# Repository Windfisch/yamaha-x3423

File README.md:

Faderboard Controller for a Yamaha X3423
========================================

This project takes out the X3423 motorized faderboard from a Yamaha 01v96 mixer and lets you wire it
up via USB. Additionally, it will have a display for each two faders that can display information
such as the assigned control.

Features right now:
	- Fader values are sent and received via MIDI CCs 1-17; sending a CC via MIDI will move the
	  fader to the respective position.
	- Integrating position regulator allows precise movement of the faders (which would otherwise
	  stop a bit before the actual target position due to friction).
	- Faders can work continously or in discrete steps; CCs 71-87 control the number of steps (where
	  0 means "continuous").
	- Calibration data is stored to flash. Perform a calibration by sending CC 100.

Hardware setup
--------------

Use a 1.25 pitch FFC A ribbon cable with 34 pins (*Note: these are quite difficult to get, I bought
a 40-lane-cable and cut it down.*) to connect the PCB with the faderboard on CN001; either use the
proper connector (*not JST*) to connect J12 with CN002, or solder an appropriate connector/cables to
CN002. Connect J16 and J17 to a buck/boost converter accepting 16V and outputting +15V/-15V, e.g.
DD39AJPA (DD1912PA should work too) from your favourite chinese marketplace.

Be sure to simultaneously power up both the main PSU and the USB board for now.

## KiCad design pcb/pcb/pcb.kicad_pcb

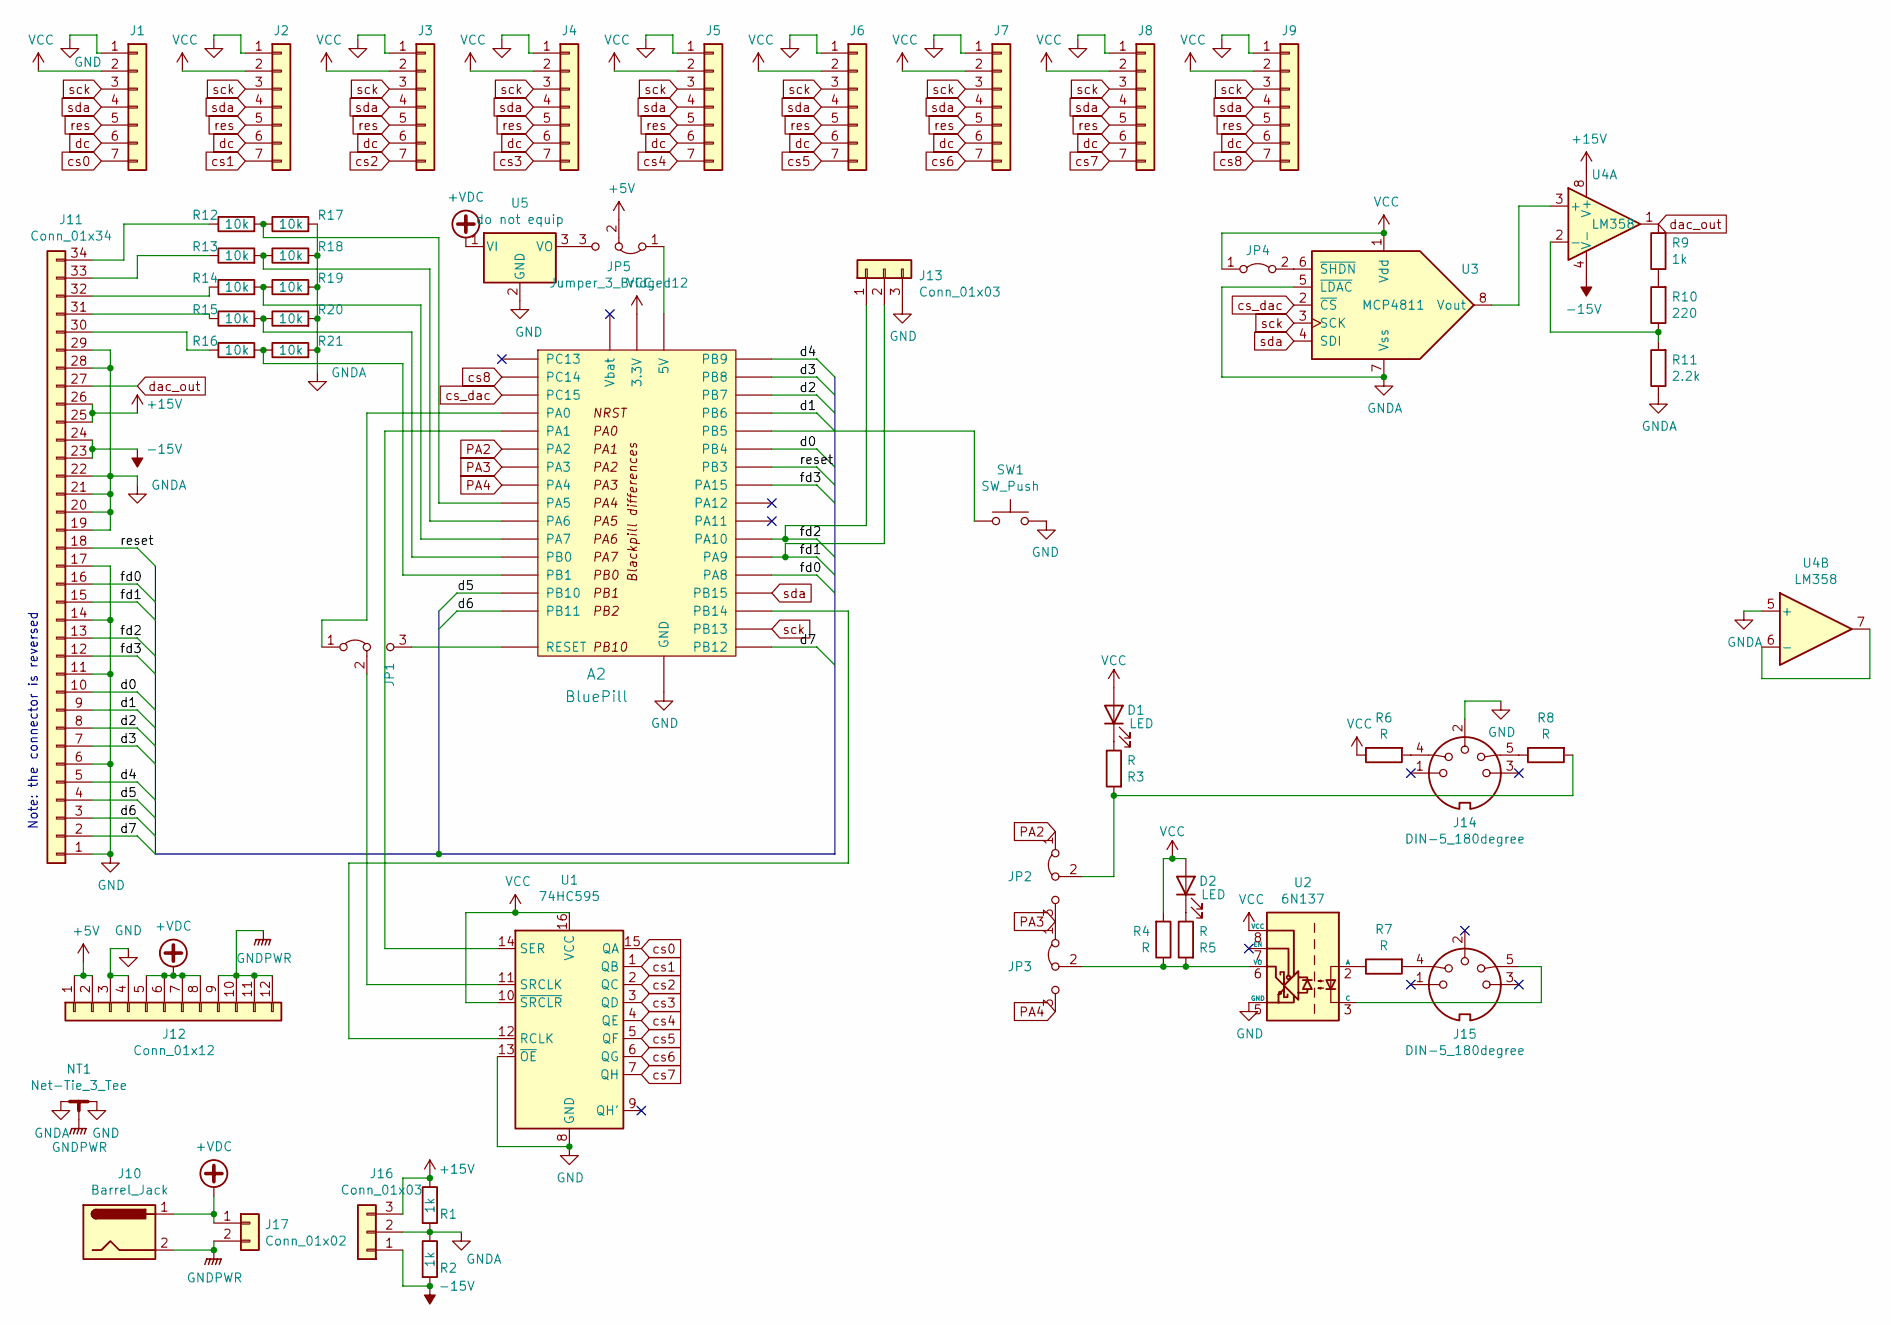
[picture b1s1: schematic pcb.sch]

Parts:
A2: BluePill; BLUEPILL-blackpill
D1, D2: LED; LED_D3.0mm_Horizontal_O1.27mm_Z2.0mm_IRBlack
J1, J2, J3, J4, J5, J6, J7, J8, J9: Conn_01x07; JST_XH_B7B-XH-A_1x07_P2.50mm_Vertical
J10: Barrel_Jack; BarrelJack_CUI_PJ-063AH_Horizontal
J11: Conn_01x34; Molex_52044_3445
J12: Conn_01x12; JST_PH_B12B-PH-K_1x12_P2.00mm_Vertical
J13: Conn_01x03; PinHeader_1x03_P2.54mm_Horizontal
J14, J15: DIN-5_180degree; DIN5
J16: Conn_01x03; JST_XH_B3B-XH-A_1x03_P2.50mm_Vertical
J17: Conn_01x02; JST_XH_B2B-XH-A_1x02_P2.50mm_Vertical
JP1, JP2, JP3, JP5: Jumper_3_Bridged12; SolderDipJumper3alt
JP4: Jumper_2_Bridged; SolderDipJumper2alt
NT1: Net-Tie_3_Tee; NetTie-3_SMD_Pad0.5mm
R1, R2, R9: 1k; R_0805_2012Metric
R3, R4, R5, R6, R7, R8: R; R_0805_2012Metric
R10: 220; R_0805_2012Metric
R11: 2.2k; R_0805_2012Metric
R12, R13, R14, R15, R16, R17, R18, R19, R20, R21: 10k; R_0805_2012Metric
SW1: SW_Push; SW_Tactile_Straight_KSL0Axx1LFTR
U1: 74HC595; DIP-16_W7.62mm
U2: 6N137; DIP-8_W7.62mm
U3: MCP4811; DIP-8_W7.62mm
U4: LM358; DIP-8_W7.62mm
U5: do not equip; TO-220-3_Horizontal_TabDown

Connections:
+5V: J12.1, J12.2, JP5.2 (C)
+15V: J11.25, J11.26, J16.3, R1.1, U4.8 (V+)
+VDC: J10.1, J12.5, J12.6, J12.7, J12.8, J17.1, U5.1 (VI)
-15V: J11.23, J11.24, J16.1, R2.2, U4.4 (V-)
/d0: A2.PB4, J11.10
/d1: A2.PB6, J11.9
/d2: A2.PB7, J11.8
/d3: A2.PB8, J11.7
/d4: A2.PB9, J11.5
/d5: A2.PB10, J11.4
/d6: A2.PB11, J11.3
/d7: A2.PB12, J11.2
/fd0: A2.PA8, J11.16
/fd1: A2.PA9, J11.15, J13.2
/fd2: A2.PA10, J11.13, J13.1
/fd3: A2.PA15, J11.12
/reset: A2.PB3, J11.18
GND: A2.G (GND), J1.1, J2.1, J3.1, J4.1, J5.1, J6.1, J7.1, J8.1, J9.1, J11.1, J11.6, J11.11, J11.14, J11.17, J12.3, J12.4, J13.3, J14.2, NT1.2, SW1.1, U1.8 (GND), U1.13 (~OE), U2.5 (GND), U5.2 (GND)
GNDA: J11.19, J11.20, J11.21, J11.22, J11.28, J11.29, J16.2, NT1.1, R1.2, R2.1, R11.1, R17.2, R18.2, R19.2, R20.2, R21.2, U3.5 (~LDAC), U3.7 (Vss), U4.5 (+)
GNDPWR: J10.2, J12.9, J12.10, J12.11, J12.12, J17.2, NT1.3
unnamed: A2.5V, JP5.1 (A)
unnamed: A2.NRST (RESET), JP1.3 (B)
unnamed: A2.PA0, JP1.1 (A)
unnamed: A2.PA1, U1.14 (SER)
unnamed: A2.PA5, R12.2, R17.1
unnamed: A2.PA6, R13.2, R18.1
unnamed: A2.PA7, R14.2, R19.1
unnamed: A2.PB0, R15.2, R20.1
unnamed: A2.PB1, R16.2, R21.1
unnamed: A2.PB5, SW1.2
unnamed: A2.PB14, U1.12 (RCLK)
unnamed: D1.1 (K), R3.1
unnamed: D2.1 (K), R5.1
unnamed: J11.30, R16.1
unnamed: J11.31, R15.1
unnamed: J11.32, R14.1
unnamed: J11.33, R13.1
unnamed: J11.34, R12.1
unnamed: J14.4, R6.2
unnamed: J14.5, R8.1
unnamed: J15.4, R7.2
unnamed: J15.5, U2.3 (C)
unnamed: JP1.2 (C), U1.11 (SRCLK)
unnamed: JP2.2 (C), R3.2, R8.2
unnamed: JP3.2 (C), R4.1, R5.2, U2.6 (VO)
unnamed: JP4.2 (B), U3.6 (~SHDN)
unnamed: JP5.3 (B), U5.3 (VO)
unnamed: R7.1, U2.2 (A)
unnamed: R10.1, R11.2, U4.2 (-)
unnamed: R9.1, R10.2
unnamed: U3.8 (Vout), U4.3 (+)
unnamed: U4.6 (-), U4.7
PA2: A2.PA2, JP2.1 (A)
PA3: A2.PA3, JP2.3 (B), JP3.1 (A)
PA4: A2.PA4, JP3.3 (B)
VCC: A2.3V3 (3.3V), D1.2 (A), D2.2 (A), J1.2, J2.2, J3.2, J4.2, J5.2, J6.2, J7.2, J8.2, J9.2, JP4.1 (A), R4.2, R6.1, U1.10 (~SRCLR), U1.16 (VCC), U2.8 (VCC), U3.1 (Vdd)
cs0: J1.7, U1.15 (QA)
cs1: J2.7, U1.1 (QB)
cs2: J3.7, U1.2 (QC)
cs3: J4.7, U1.3 (QD)
cs4: J5.7, U1.4 (QE)
cs5: J6.7, U1.5 (QF)
cs6: J7.7, U1.6 (QG)
cs7: J8.7, U1.7 (QH)
cs8: A2.PC14, J9.7
cs_dac: A2.PC15, U3.2 (~CS)
dac_out: J11.27, R9.2, U4.1
dc: J1.6, J2.6, J3.6, J4.6, J5.6, J6.6, J7.6, J8.6, J9.6
res: J1.5, J2.5, J3.5, J4.5, J5.5, J6.5, J7.5, J8.5, J9.5
sck: A2.PB13, J1.3, J2.3, J3.3, J4.3, J5.3, J6.3, J7.3, J8.3, J9.3, U3.3 (SCK)
sda: A2.PB15, J1.4, J2.4, J3.4, J4.4, J5.4, J6.4, J7.4, J8.4, J9.4, U3.4 (SDI)

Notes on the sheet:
Note: the connector is reversed

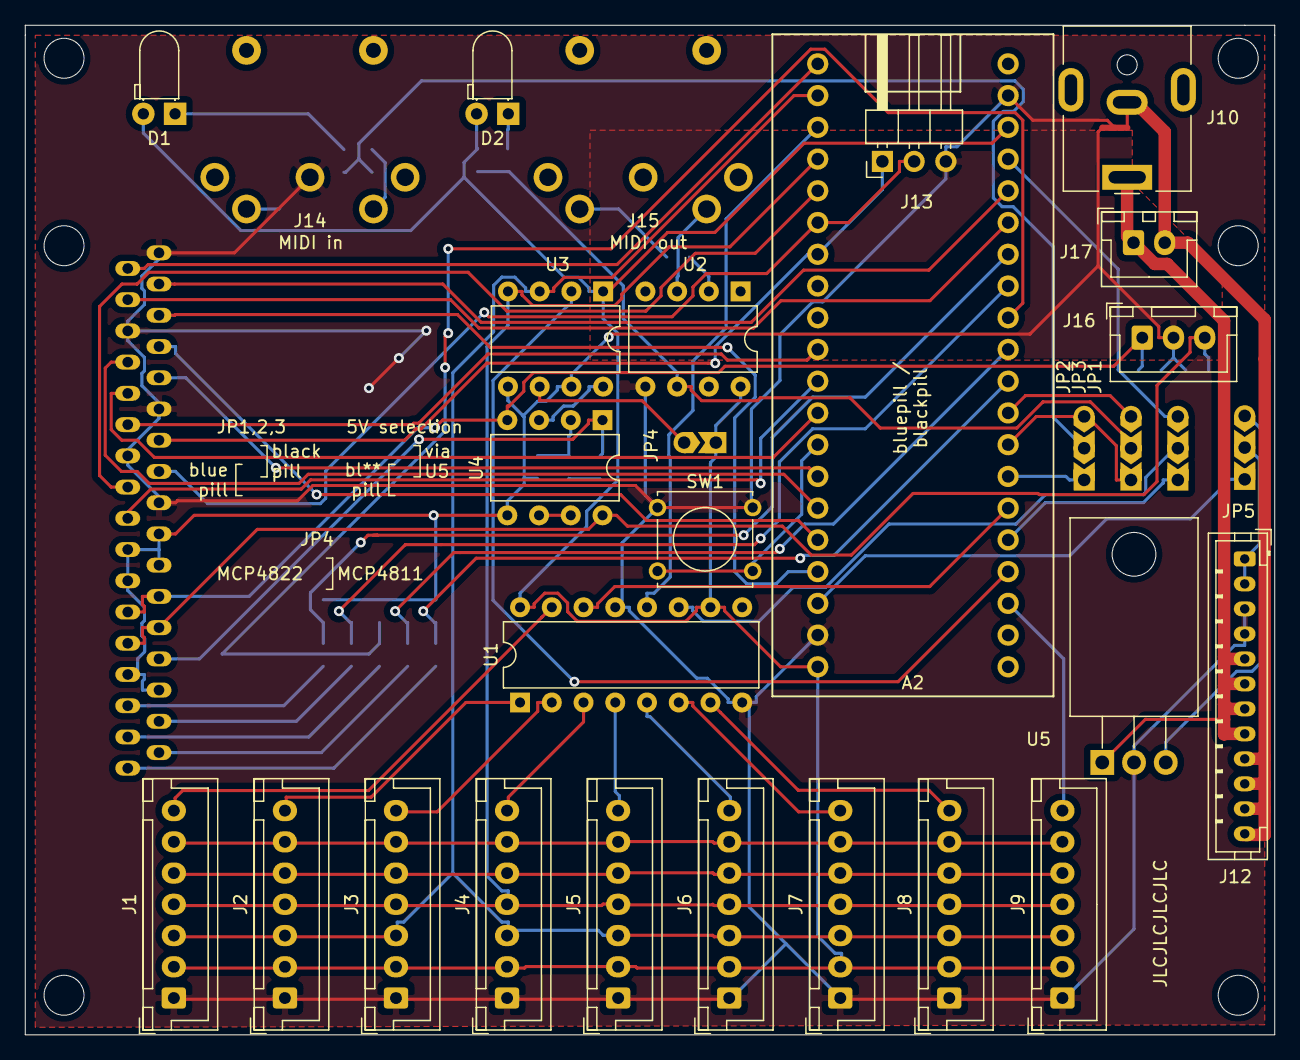
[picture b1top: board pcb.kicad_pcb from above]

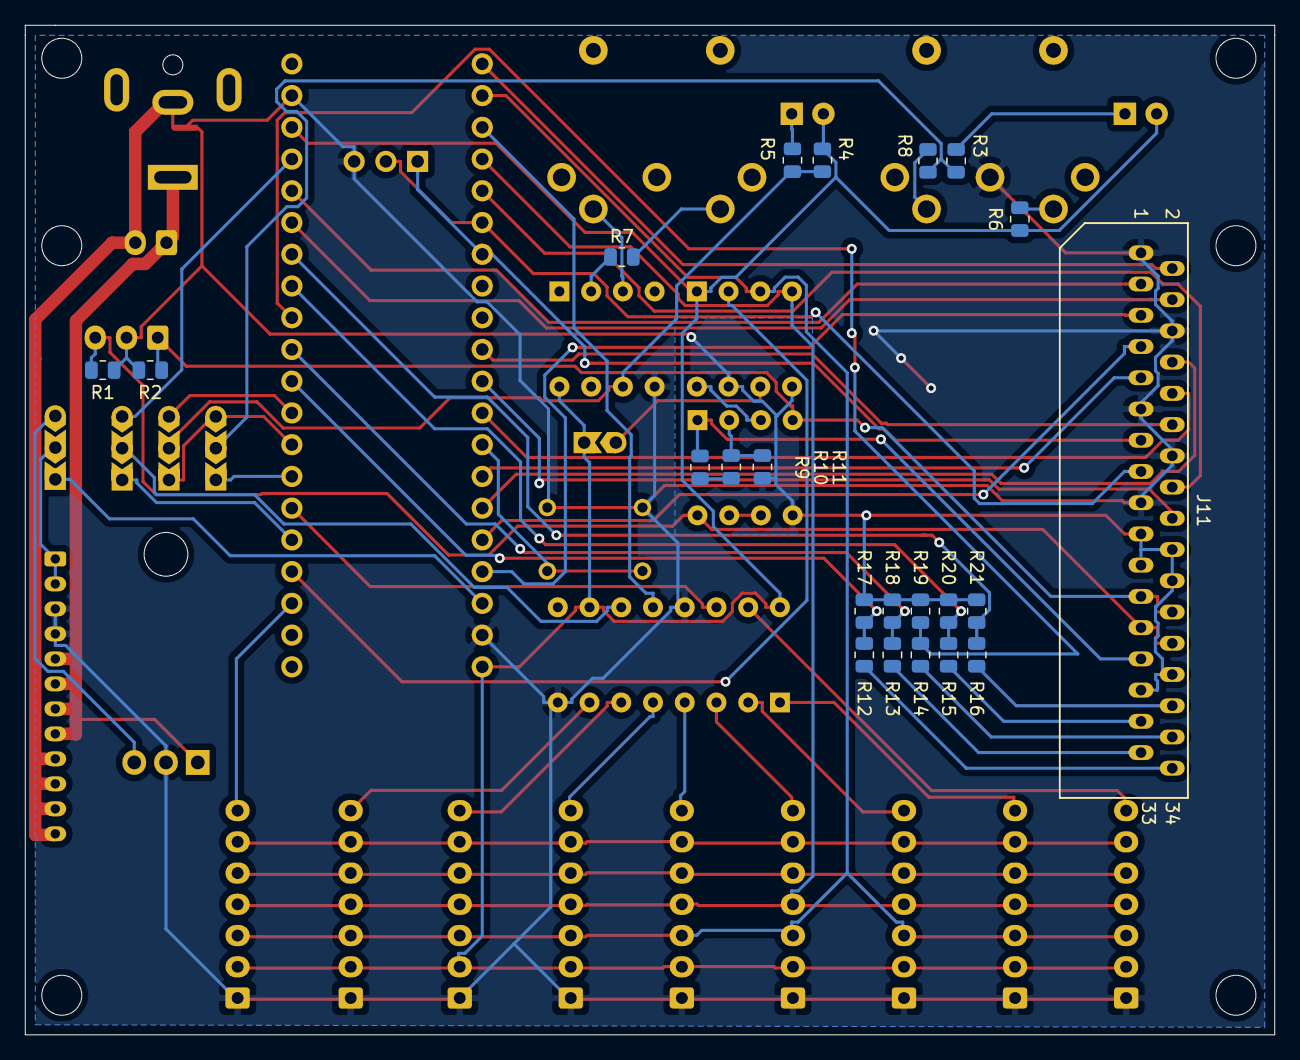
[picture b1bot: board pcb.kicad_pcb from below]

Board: 2 copper layers, 100.0 x 80.8 mm, 59 parts (22 on the bottom side), 71 nets.

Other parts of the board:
hole1, hole1#2, hole2, hole2#2, hole3, hole4: MountingHole_3.2mm_M3_DIN965

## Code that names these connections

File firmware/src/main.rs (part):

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


type ShiftRegisterType = shift_register::ShiftRegister<PB14<Output<PushPull>>, PA0<Output<PushPull>>, PA1<Output<PushPull>>>;
type ShiftRegisterPin = shift_register::Pin<'static, PB14<Output<PushPull>>, PA0<Output<PushPull>>, PA1<Output<PushPull>>>;



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	}
}

type SpiType = spi::Spi<stm32f1xx_hal::pac::SPI2, spi::Spi2NoRemap, (PB13<Alternate<PushPull>>, spi::NoMiso, PB15<Alternate<PushPull>>), u8>;

#[app(device = stm32f1xx_hal::pac, peripherals = true)]
const APP: () = {
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
		usb_dev: UsbDevice<'static, UsbBusType>,
		midi: usbd_midi::midi_device::MidiClass<'static, UsbBus<Peripheral>>,
		dac: Mcp49xx<SpiInterface<SharedBus<SpiType>, OldOutputPin<PC15<Output<PushPull>>>>, Resolution12Bit, DualChannel, Unbuffered>,

		sysex_buffer_mainthread: &'static panic_mutex::PanicMutex<SysexBuffer<SYSEX_BUFFER_SIZE>>,
		sysex_buffer_usb: &'static panic_mutex::PanicMutex<SysexBuffer<SYSEX_BUFFER_SIZE>>,
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			ssd1306::Ssd1306<
				ssd1306::prelude::SPIInterface<
					SharedBus<SpiType>,
					shared_gpio::SharedGpio<PB5<Output<PushPull>>>,
					RefMutOutputPin<'static, dyn embedded_hal::digital::v2::OutputPin<Error = Infallible> + Send>
				>,
				ssd1306::size::DisplaySize128x64,
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		let mut gpioa = device.GPIOA.split(&mut rcc.apb2);
		let mut gpiob = device.GPIOB.split(&mut rcc.apb2);
		let mut gpioc = device.GPIOC.split(&mut rcc.apb2);
		let (pa15, pb3, pb4) = afio.mapr.disable_jtag(gpioa.pa15, gpiob.pb3, gpiob.pb4);
		let mut led = gpioc
			.pc13
			.into_push_pull_output_with_state(&mut gpioc.crh, State::Low);
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

		// Configure SPI
		let mosi = gpiob.pb15.into_alternate_push_pull(&mut gpiob.crh);
		let sck = gpiob.pb13.into_alternate_push_pull(&mut gpiob.crh);
		let spi: SpiType = spi::Spi::spi2(device.SPI2, (sck, spi::NoMiso, mosi), spi::Mode { phase : spi::Phase::CaptureOnFirstTransition, polarity : spi::Polarity::IdleLow }, 10.mhz(), clocks, &mut rcc.apb1);

		let shared_spi = shared_bus_rtic::new!(spi, SpiType);
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			// Configure display
			let chip_selects = {
				// Configure shift register
				let shiftreg_data = gpioa.pa1.into_push_pull_output(&mut gpioa.crl);
				let shiftreg_clock = gpioa.pa0.into_push_pull_output(&mut gpioa.crl); // on black pill, this is pb10
				let shiftreg_latch = gpiob.pb14.into_push_pull_output(&mut gpiob.crh);
				let shift_register = shift_register::ShiftRegister::new(shiftreg_latch, shiftreg_clock, shiftreg_data, 0xFF);
				let cs_0to7 = cortex_m::singleton!(: [ShiftRegisterPin; 8] = {
					shift_register::ShiftRegister::split(panic_mutex::new!(shift_register; ShiftRegisterType))
				}).unwrap();
			
				// Configure the 9th chip select pin
				let pc14 = gpioc.pc14.into_push_pull_output(&mut gpioc.crh);
				let cs8 = cortex_m::singleton!(: PC14<Output<PushPull>> = pc14).unwrap();
				cs8.set_high();

				cs_0to7.iter_mut()
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					.chain(core::iter::once(cs8 as _))
			};

			let display_dc = shared_gpio::SharedGpio(panic_mutex::new!(gpiob.pb5.into_push_pull_output(&mut gpiob.crl); PB5<Output<PushPull>>));

			let mut displays = chip_selects.map(|cs|
				ssd1306::Ssd1306::new(
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			display.init_with_addr_mode(ssd1306::command::AddrMode::Horizontal).unwrap();
		}

		let dac_cs: OldOutputPin<_> = gpioc.pc15.into_push_pull_output_with_state(&mut gpioc.crh, State::High).into();
		let dac = mcp49xx::Mcp49xx::new_mcp4822(shared_spi.acquire(), dac_cs);

		let adc = stm32f1xx_hal::adc::Adc::adc1(device.ADC1, &mut rcc.apb2, clocks);
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		let mut resources = init::LateResources {
			led,
			x3423: X3423::new(x3423::X3423Resources {
				mfpos0: gpioa.pa5.into_analog(&mut gpioa.crl),
				mfpos1: gpioa.pa6.into_analog(&mut gpioa.crl),
				mfpos2: gpioa.pa7.into_analog(&mut gpioa.crl),
				mfpos3: gpiob.pb0.into_analog(&mut gpiob.crl),
				mfpos4: gpiob.pb1.into_analog(&mut gpiob.crl),
				reset: pb3.into_open_drain_output_with_state(&mut gpiob.crl, State::Low),
				fd0: gpioa.pa8.into_open_drain_output(&mut gpioa.crh),
				fd1: gpioa.pa9.into_open_drain_output(&mut gpioa.crh),
				fd2: gpioa.pa10.into_open_drain_output(&mut gpioa.crh),
				fd3: pa15.into_open_drain_output(&mut gpioa.crh),
				data: x3423::X3423DataPins {
					d0: pb4.into_open_drain_output(&mut gpiob.crl),
					d1: gpiob.pb6.into_open_drain_output(&mut gpiob.crl),
					d2: gpiob.pb7.into_open_drain_output(&mut gpiob.crl),
					d3: gpiob.pb8.into_open_drain_output(&mut gpiob.crh),
					d4: gpiob.pb9.into_open_drain_output(&mut gpiob.crh),
					d5: gpiob.pb10.into_open_drain_output(&mut gpiob.crh),
					d6: gpiob.pb11.into_open_drain_output(&mut gpiob.crh),
					d7: gpiob.pb12.into_open_drain_output(&mut gpiob.crh),
				},
				adc,
			}),
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
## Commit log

2020-12-30 initial commit, test accessing the flipflops
2020-12-30 read out the fader values
2020-12-30 moving the faders to zero works!
2021-06-13 Schematic
2021-06-15 pcb++
2021-06-16 Maybe finished PCB layout
2021-06-18 silkscreen
2021-07-16 First firmware attempts
2021-07-16 Add license to Cargo.toml
2021-07-16 Setting fader values \o/
2021-07-16 Set faders to a sine pattern
2021-07-16 Animated sine pattern :D
2021-07-21 Copy values from fader 1 to fader 2
2021-07-21 Fix bug
2021-07-21 Copy more values, testing all dacs
2021-07-21 fix hardware bug
2021-07-22 Add usb support
2021-07-22 Send fader values to MIDI
2021-07-23 input calibration
2021-07-23 Set fader values
2021-07-23 Turn mainloop into periodic interrupt
2021-07-23 output calibration
2021-07-23 PI-regulator for the position
2021-07-23 fixed usb lockups
2021-07-23 steppiness
2021-07-23 Allow USB to override steppiness
2021-07-23 Refactor: move x3423 module out
2021-07-23 Fix warnings
2021-07-23 More refactoring
2021-07-24 Fix all warnings
2021-07-24 factor out fader.rs
2021-07-24 Save calibration data to flash
2021-07-24 README
2021-07-24 Fix usb lockups
2021-08-18 do not overwrite the calibration data when flashing
2021-08-18 add clear_target()
2021-08-18 work around flash bug
2021-08-18 "slow fader" effect and manual control
2021-08-18 Fix jump back
2021-08-18 Fix calibration bug and improve motor limiter
2021-08-18 Optimize Queue
2021-08-18 Only process faders when not calibrating
2021-08-19 The Great Refactor
2021-08-19 Fix most bugs (hopefully)
2021-08-19 commented out state inertia (does not work)
2021-08-19 tune fader pid
2021-08-19 reduce slew rate
2021-08-19 Revert "commented out state inertia (does not work)"
    This reverts commit d4947a1c5d31e7677b48b715f2da753856834bb9.
2021-08-19 Revert "tune fader pid"
    This reverts commit 52b091be73a6b15411318ec79f1637854290e2f0.
2021-08-19 fix last bugs
2021-08-19 jump timeout
2021-08-19 support 14 bit controller inputs
2022-01-13 First case drawings
2022-01-13 Reference drawing
2022-01-13 Intermediate commit
2022-01-13 Finished?
2022-01-13 Finished!
2022-01-14 laser svg file;
2023-07-20 Display works
2023-07-21 text test
2023-07-25 Mutex, shared bus/gpio and shift register
2023-07-25 Shift register works :)
2023-07-26 looks like generic multiple displays could work?
2023-07-27 Confirmed that it works on display 2, too
2023-07-28 fix shared_gpio
2023-07-28 Attempt to have a displays array, but the RAM is too small
2023-07-28 it works!!
2023-07-29 draw to all displays
2023-07-30 Improve display of calibration status
2023-08-05 Receive graphics via sysex
2023-08-06 clean up and fix concurrency issue
2023-09-16 new display tool
2023-09-18 Tune compiler flags
2023-09-18 Reduce history queue length
